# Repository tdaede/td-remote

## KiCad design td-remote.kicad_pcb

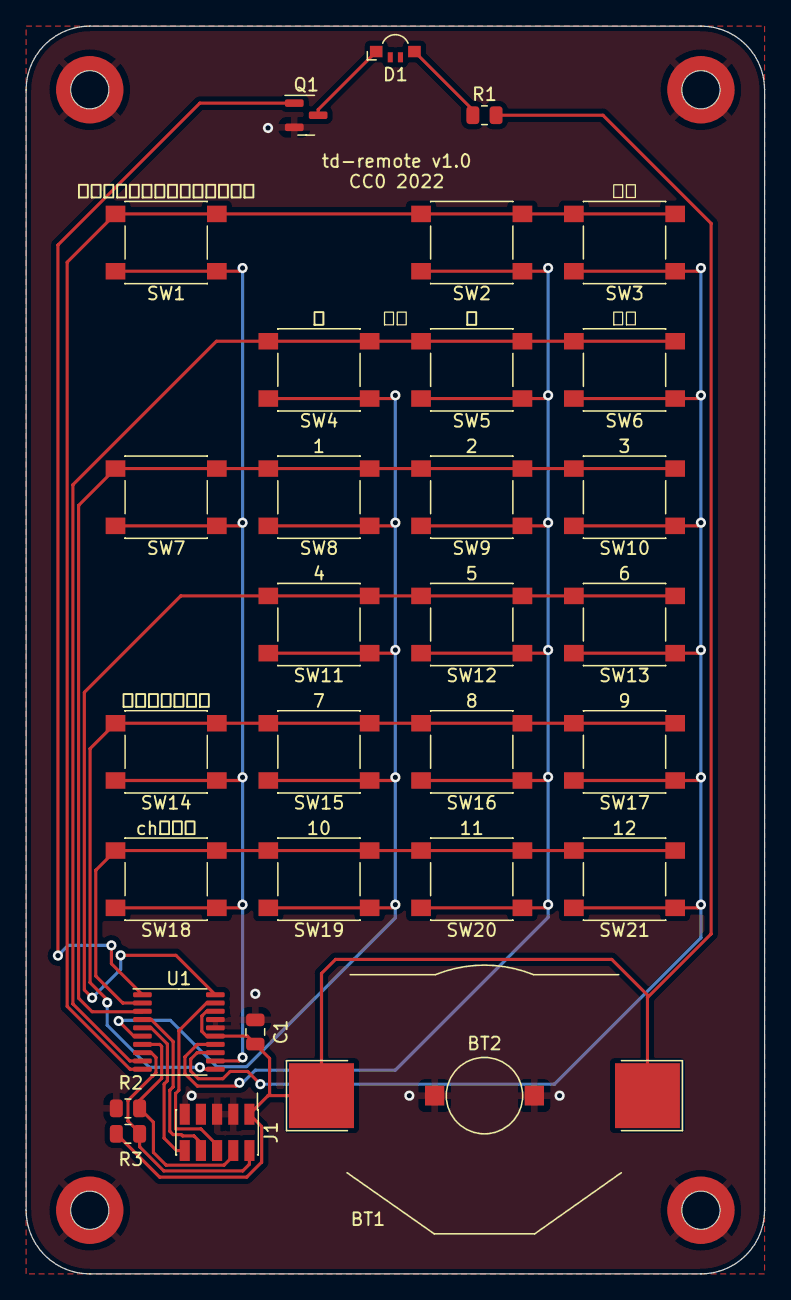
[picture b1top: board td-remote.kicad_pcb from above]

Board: 2 copper layers, 58.0 x 98.0 mm, 35 parts (0 on the bottom side), 20 nets.

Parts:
BT1: Battery_Cell; BatteryHolder_Keystone_3002_1x2032_noneg
BT2: Battery_Cell; BatteryHolder_Keystone_2991TR
C1: 0.1uF; C_0805_2012Metric
D1: APA3010F3C-GX; LED_Kingbright_APFA3010_3x1.5mm_Horizontal
H1, H2, H3, H4: 9774035243R; WA-SMST-M2
J1: Conn_ARM_JTAG_SWD_10; 20021122-00010T4LF
Q1: BSS138; SOT-23
R1: 39; R_0805_2012Metric
R2, R3: 100k; R_0805_2012Metric
SW1, SW2, SW3, SW4, SW5, SW6, SW7, SW8, SW9, SW10, SW11, SW12, SW13, SW14, SW15, SW16, SW17, SW18, SW19, SW20, SW21: 2223-TS04-66-65-BK-100-SMT; SW_SPST_PTS645
U1: LPC822M101JDH20; TSSOP-20_4.4x6.5mm_P0.65mm

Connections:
+BATT: BT1.1 (+), C1.1, J1.1 (VTref), R1.2, R3.1, U1.15 (VDD), U1.18 (VREFP)
/col0: SW1.2, SW7.2, SW14.2, SW18.2, U1.12 (PIO0_1)
/col1: SW4.2, SW8.2, SW11.2, SW15.2, SW19.2, U1.6 (PIO0_4)
/col2: SW2.2, SW5.2, SW9.2, SW12.2, SW16.2, SW20.2, U1.14 (PIO0_8)
/col3: SW3.2, SW6.2, SW10.2, SW13.2, SW17.2, SW21.2, U1.13 (PIO0_9)
/out: Q1.1 (G), U1.1 (PIO0_23)
/row0: SW1.1, SW2.1, SW3.1, U1.10 (PIO0_10)
/row1: SW4.1, SW5.1, SW6.1, U1.9 (PIO0_11)
/row2: SW7.1, SW8.1, SW9.1, SW10.1, U1.3 (PIO0_13)
/row3: SW11.1, SW12.1, SW13.1, U1.20 (PIO0_14)
/row4: SW14.1, SW15.1, SW16.1, SW17.1, U1.11 (PIO0_15)
/row5: SW18.1, SW19.1, SW20.1, SW21.1, U1.2 (PIO0_17)
/tck: J1.4 (SWDCLK/TCK), R2.1, U1.7 (PIO0_3)
/tdi: J1.8 (NC/TDI), U1.4 (PIO0_12)
/tdo: J1.6 (SWO/TDO), U1.19 (PIO0_0)
/tms: J1.2 (SWDIO/TMS), R3.2, U1.8 (PIO0_2)
/~reset: J1.10 (~RESET), U1.5 (PIO0_5)
GND: BT2.2 (-), C1.2, H1.1, H2.1, H3.1, H4.1, J1.3 (GND), J1.5 (GND), J1.9 (GNDDetect), Q1.2 (S), R2.2, U1.16 (VSS), U1.17 (VREFN)
unnamed: D1.1 (K), Q1.3 (D)
unnamed: D1.2 (A), R1.1

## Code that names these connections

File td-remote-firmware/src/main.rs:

#![no_main]
#![no_std]

use panic_halt as _;

use bitvec::prelude::*;
use lpc8xx_hal::{
    cortex_m::interrupt as _interrupt, cortex_m_rt::entry, pac::interrupt as interrupt,  delay::Delay, gpio::Level, gpio::GpioPin, gpio::direction, prelude::*, CorePeripherals, pac::NVIC, pac::Interrupt,
    Peripherals
};

// tuned to create 38kHz modulation
const MODULATION_PERIOD: u16 = 18;

fn send_1ms_pulse<P>(delay: &mut Delay, led: &mut GpioPin<P, direction::Output>) where P: lpc8xx_hal::pins::Trait {
    for _ in 0..12 {
        led.set_high();
        delay.delay_us(MODULATION_PERIOD * 2 / 4);
        led.set_low();
        delay.delay_us(MODULATION_PERIOD * 2 / 4);
    }
    delay.delay_us(680 as u16);
}

fn send_2ms_pulse<P>(delay: &mut Delay, led: &mut GpioPin<P, direction::Output>) where P: lpc8xx_hal::pins::Trait {
    for _ in 0..12 {
        led.set_high();
        delay.delay_us(MODULATION_PERIOD * 2 / 4);
        led.set_low();
        delay.delay_us(MODULATION_PERIOD * 2 / 4);
    }
    delay.delay_us(1680_u16);
}

const CODE_ARRAY: [[u16; 4]; 6] = [
    [0b01000, 0b00000, 0b01101, 0b01110],
    [0b00000, 0b00010, 0b00001, 0b00110],
    [0b01111, 0b10000, 0b10001, 0b10010],
    [0b00000, 0b10011, 0b10100, 0b10101],
    [0b01001, 0b10110, 0b10111, 0b11000],
    [0b00100, 0b11001, 0b11010, 0b11011],
];

fn send_code<P>(code: u16, delay: &mut Delay, led: &mut GpioPin<P, direction::Output>) where P: lpc8xx_hal::pins::Trait  {
    // first code
    send_1ms_pulse(delay, led);
    send_1ms_pulse(delay, led);
    send_1ms_pulse(delay, led);
    for bit in code.view_bits::<Lsb0>().iter().take(9) {
        if *bit {
            send_2ms_pulse(delay, led);
        } else {
            send_1ms_pulse(delay, led);
        }
    }
    send_1ms_pulse(delay, led); // trailing pulse
    delay.delay_ms(40_u16);
    // second code
    send_1ms_pulse(delay, led);
    send_1ms_pulse(delay, led);
    send_1ms_pulse(delay, led);
    for bit in code.view_bits::<Lsb0>().iter().take(9) {
        if *bit {
            send_1ms_pulse(delay, led);
        } else {
            send_2ms_pulse(delay, led);
        }
    }
    send_1ms_pulse(delay, led); // trailing pulse
    delay.delay_ms(40_u16);
}

fn pin_interrupt_handler() {
}

#[interrupt]
fn PIN_INT0() {
    pin_interrupt_handler();
}
#[interrupt]
fn PIN_INT1() {
    pin_interrupt_handler();
}
#[interrupt]
fn PIN_INT2() {
    pin_interrupt_handler();
}
#[interrupt]
fn PIN_INT3() {
    pin_interrupt_handler();
}

#[entry]
fn main() -> ! {
    let cp = CorePeripherals::take().unwrap();
    let p = Peripherals::take().unwrap();

    // Initialize the APIs of the peripherals we need.
    let mut delay = Delay::new(cp.SYST);

    let syscon = p.SYSCON.free();

    syscon.sysahbclkctrl.modify(|_, w| w.iocon().set_bit());

    let iocon = p.IOCON;
    // first two pins use "i2c" mode for open drain
    // it is absolutely critical for low power that pullups are disabled
    iocon.pio0_10.modify(|_, w| w.i2cmode().standarad_i2c());
    iocon.pio0_11.modify(|_, w| w.i2cmode().standarad_i2c());
    iocon.pio0_13.modify(|_, w| w.od().enabled().mode().inactive());
    iocon.pio0_14.modify(|_, w| w.od().enabled().mode().inactive());
    iocon.pio0_15.modify(|_, w| w.od().enabled().mode().inactive());
    iocon.pio0_17.modify(|_, w| w.od().enabled().mode().inactive());
    iocon.pio0_23.modify(|_, w| w.mode().inactive());
    iocon.pio0_3.modify(|_, w| w.mode().inactive()); // external pulldown is provided here

    let gpio = p.GPIO; // GPIO is initialized by default on LPC82x.

    let (led, token) = (p.pins.pio0_23, gpio.tokens.pio0_23);

    let pinint = p.PININT;
    unsafe {
        syscon.pintsel[0].write(|w| w.intpin().bits(1));
        syscon.pintsel[1].write(|w| w.intpin().bits(4));
        syscon.pintsel[2].write(|w| w.intpin().bits(8));
        syscon.pintsel[3].write(|w| w.intpin().bits(9));
    }
    //syscon.sysahbclkctrl.modify(|_, w| w.gpio().set_bit()); // this should already be enabled
    syscon.starterp0.modify(|_,w| w.pint0().enabled().pint1().enabled().pint2().enabled().pint3().enabled());
    unsafe {
        pinint.isel.write(|w| w.pmode().bits(0b00001111)); // level sensitive
        pinint.ienf.write(|w| w.enaf().bits(0b00000000)); // low level sensitive interrupt
        pinint.ienr.write(|w| w.enrl().bits(0b00001111)); // enable interrupt
    }

    let mut led = led.into_output_pin(token, Level::Low);

    let mut row0 = p.pins.pio0_10.into_output_pin(gpio.tokens.pio0_10, Level::High);
    let mut row1 = p.pins.pio0_11.into_output_pin(gpio.tokens.pio0_11, Level::High);
    let mut row2 = p.pins.pio0_13.into_output_pin(gpio.tokens.pio0_13, Level::High);
    let mut row3 = p.pins.pio0_14.into_output_pin(gpio.tokens.pio0_14, Level::High);
    let mut row4 = p.pins.pio0_15.into_output_pin(gpio.tokens.pio0_15, Level::High);
    let mut row5 = p.pins.pio0_17.into_output_pin(gpio.tokens.pio0_17, Level::High);

    let col0 = p.pins.pio0_1.into_input_pin(gpio.tokens.pio0_1);
    let col1 = p.pins.pio0_4.into_input_pin(gpio.tokens.pio0_4);
    let col2 = p.pins.pio0_8.into_input_pin(gpio.tokens.pio0_8);
    let col3 = p.pins.pio0_9.into_input_pin(gpio.tokens.pio0_9);

    let mut scb = cp.SCB;
    let mut pmu = p.PMU.split().handle;

    _interrupt::free(|_| {
        unsafe {
            NVIC::unmask(Interrupt::PIN_INT0);
            NVIC::unmask(Interrupt::PIN_INT1);
            NVIC::unmask(Interrupt::PIN_INT2);
            NVIC::unmask(Interrupt::PIN_INT3);
        }

        loop {
            for row in 0..6 {
                match row {
                    0 => row0.set_low(),
                    1 => row1.set_low(),
                    2 => row2.set_low(),
                    3 => row3.set_low(),
                    4 => row4.set_low(),
                    5 => row5.set_low(),
                    _ => unreachable!()
                };
                for col in 0..4 {
                    let state = match col {
                        0 => col0.is_low(),
                        1 => col1.is_low(),
                        2 => col2.is_low(),
                        3 => col3.is_low(),
                        _ => unreachable!()
                    };
                    if state {
                        send_code(CODE_ARRAY[row][col], &mut delay, &mut led);
                    }
                }
                match row {
                    0 => row0.set_high(),
                    1 => row1.set_high(),
                    2 => row2.set_high(),
                    3 => row3.set_high(),
                    4 => row4.set_high(),
                    5 => row5.set_high(),
                    _ => unreachable!()
                };
            }
            // now set all rows low for interrupt purposes
            row0.set_low();
            row1.set_low();
            row2.set_low();
            row3.set_low();
            row4.set_low();
            row5.set_low();
            NVIC::unpend(Interrupt::PIN_INT0);
            NVIC::unpend(Interrupt::PIN_INT1);
            NVIC::unpend(Interrupt::PIN_INT2);
            NVIC::unpend(Interrupt::PIN_INT3);
            unsafe { pmu.enter_power_down_mode(&mut scb) };
            row0.set_high();
            row1.set_high();
            row2.set_high();
            row3.set_high();
            row4.set_high();
            row5.set_high();
        }
    })
}

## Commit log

2023-09-12 remove ist write
